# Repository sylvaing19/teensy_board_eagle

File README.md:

# teensy_board_eagle
Eagle library for integrating teensy boards.

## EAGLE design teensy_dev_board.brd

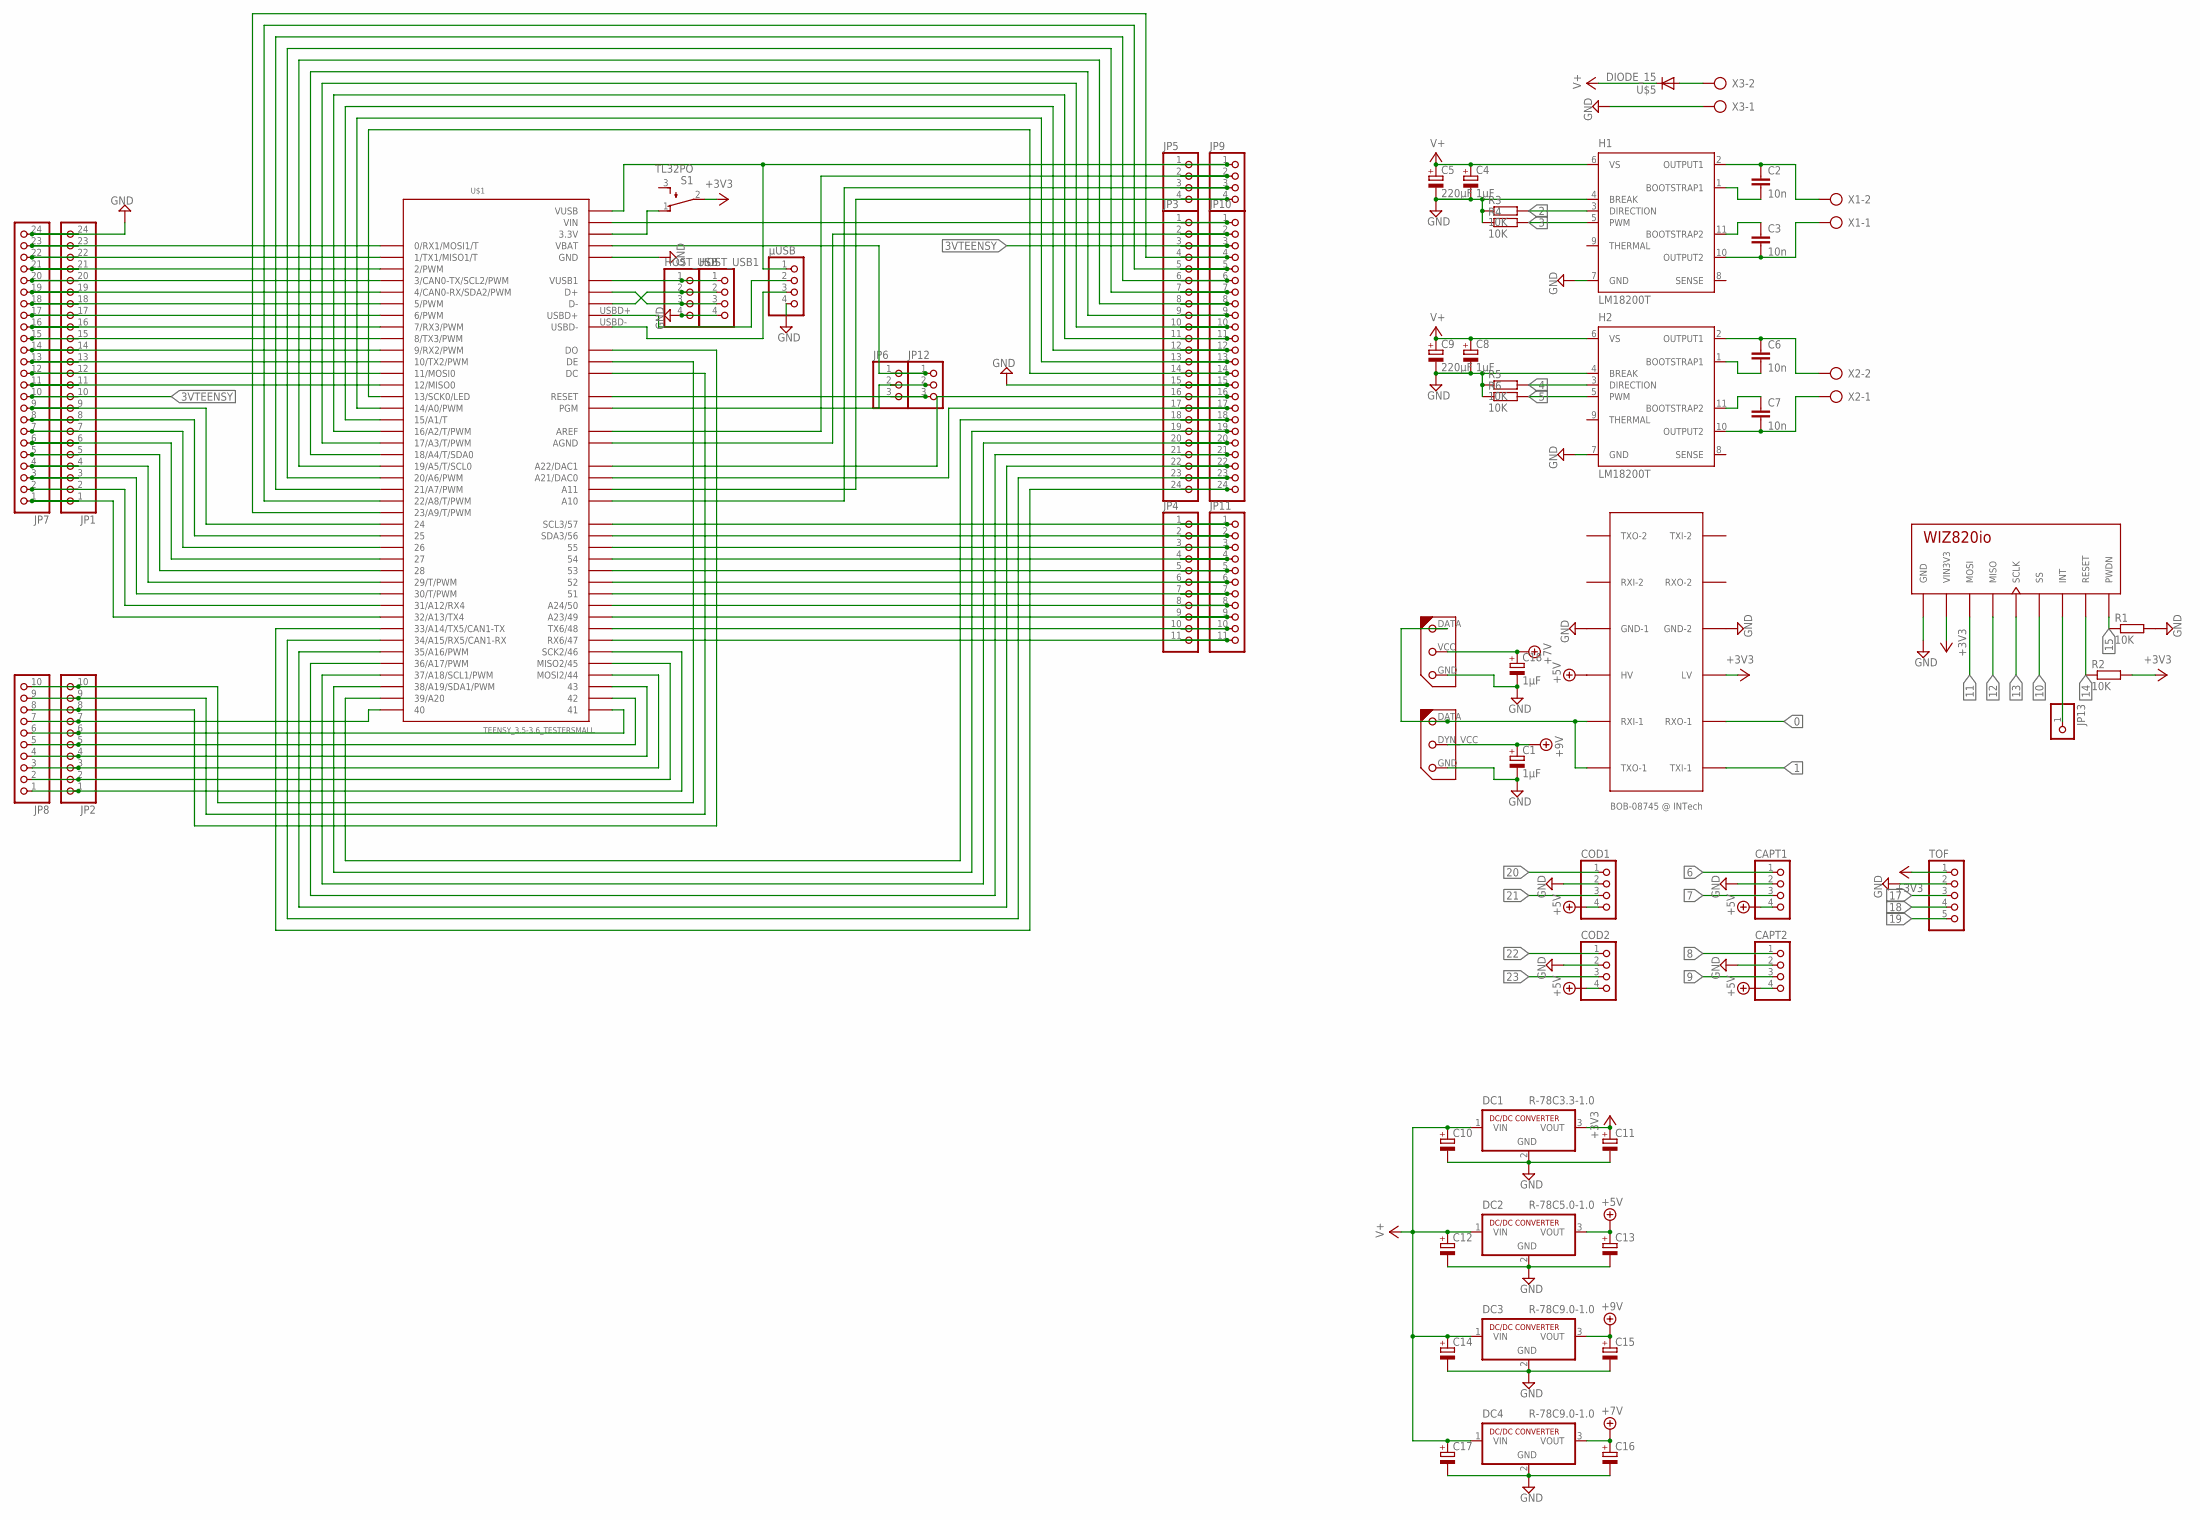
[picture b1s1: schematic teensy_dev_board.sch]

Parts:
C1, C18: 1µF; E2,5-6E
C2, C3, C6, C7: 10n; C050-025X075
C4, C8: 1µF; E2,5-7
C5, C9: 220µF; E2,5-7
C10, C11, C12, C13, C14, C15, C16, C17: CPOL-EUE2.5-6; E2,5-6
CAPT1, CAPT2: PINHD-1X4B; 1X04B
COD1, COD2: PINHD-1X4B; 1X04B
DC1: R-78C3.3-1.0; SIP3
DC2: R-78C5.0-1.0; SIP3
DC3, DC4: R-78C9.0-1.0; SIP3
H1, H2: LM18200T; TO-220-11
HOST_USB, HOST_USB1: PINHD-1X4; 1X04
JP1, JP3, JP7, JP10: PINHD-1X24; 1X24
JP2, JP8: PINHD-1X10; 1X10
JP4, JP11: PINHD-1X11; 1X11
JP5, JP9: PINHD-1X4; 1X04
JP6, JP12: PINHD-1X3; 1X03
JP13: PINHD-1X1; 1X01
R1, R2, R3, R4, R5, R6: 10K; 0204/7
S1: TL32PO; TL3XPO
TOF: PINHD-1X5B; 1X05B
U$1: TEENSY_3.5-3.6_TESTERSMALL; TEENSY_3.5-3.6_TESTER_SMALL
U$2: BOB-08745
U$3: DYNAMIXEL-1X03AX; DYNAMIXEL_AX_1X03
U$4: WIZ820IO; WIZ820
U$5: DIODE_15; DO201-15
U$6: DYNAMIXEL-1X03XL; DYNAMIXEL_XL_1X03
X1, X2, X3: AK300/2
µUSB: PINHD-1X4; 1X04

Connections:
0: JP1.23, JP7.23, U$1.0 (0/RX1/MOSI1/T), U$2.RXO-1
1: JP1.22, JP7.22, U$1.1 (1/TX1/MISO1/T), U$2.TXI-1
2: H1.3 (DIRECTION), JP1.21, JP7.21, R3.2, U$1.2 (2/PWM)
3: H1.5 (PWM), JP1.20, JP7.20, R4.2, U$1.3 (3/CAN0-TX/SCL2/PWM)
3VTEENSY: JP1.10, JP3.3, JP7.10, JP10.3, S1.1 (O), U$1.3.3V, U$1.3.3V2 (3.3V), U$1.3.3V3 (3.3V), U$1.3.3V4 (3.3V)
4: H2.3 (DIRECTION), JP1.19, JP7.19, R5.2, U$1.4 (4/CAN0-RX/SDA2/PWM)
5: H2.5 (PWM), JP1.18, JP7.18, R6.2, U$1.5 (5/PWM)
6: CAPT1.1, JP1.17, JP7.17, U$1.6 (6/PWM)
7: CAPT1.3, JP1.16, JP7.16, U$1.7 (7/RX3/PWM)
8: CAPT2.1, JP1.15, JP7.15, U$1.8 (8/TX3/PWM)
9: CAPT2.3, JP1.14, JP7.14, U$1.9 (9/RX2/PWM)
10: JP1.13, JP7.13, U$1.10 (10/TX2/PWM), U$4.SS
11: JP1.12, JP7.12, U$1.11 (11/MOSI0), U$4.MOSI
12: JP1.11, JP7.11, U$1.12 (12/MISO0), U$4.MISO
13: JP3.14, JP10.14, U$1.13 (13/SCK0/LED), U$4.SCLK
14: JP3.13, JP10.13, R2.1, U$1.14/A0 (14/A0/PWM), U$4.RESET
15: JP3.12, JP10.12, R1.1, U$1.15/A1 (15/A1/T), U$4.PWDN
16: JP3.11, JP10.11, U$1.16/A2 (16/A2/T/PWM)
17: JP3.10, JP10.10, TOF.3, U$1.17/A3 (17/A3/T/PWM)
18: JP3.9, JP10.9, TOF.4, U$1.18/A4 (18/A4/T/SDA0)
19: JP3.8, JP10.8, TOF.5, U$1.19/A5 (19/A5/T/SCL0)
20: COD1.1, JP3.7, JP10.7, U$1.20/A6 (20/A6/PWM)
21: COD1.3, JP3.6, JP10.6, U$1.21/A7 (21/A7/PWM)
22: COD2.1, JP3.5, JP10.5, U$1.22/A8 (22/A8/T/PWM)
23: COD2.3, JP3.4, JP10.4, U$1.23/A9 (23/A9/T/PWM)
24: JP1.9, JP7.9, U$1.24
25: JP1.8, JP7.8, U$1.25
26: JP1.7, JP7.7, U$1.26
27: JP1.6, JP7.6, U$1.27
28: JP1.5, JP7.5, U$1.28
29: JP1.4, JP7.4, U$1.29 (29/T/PWM)
30: JP1.3, JP7.3, U$1.30 (30/T/PWM)
31: JP1.2, JP7.2, U$1.31/A12 (31/A12/RX4)
32: JP1.1, JP7.1, U$1.32/A13 (32/A13/TX4)
33: JP3.24, JP10.24, U$1.33/A14 (33/A14/TX5/CAN1-TX)
34: JP3.23, JP10.23, U$1.34/A15 (34/A15/RX5/CAN1-RX)
35: JP3.22, JP10.22, U$1.35/A16 (35/A16/PWM)
36: JP3.21, JP10.21, U$1.36/A17 (36/A17/PWM)
37: JP3.20, JP10.20, U$1.37/A18 (37/A18/SCL1/PWM)
38: JP3.19, JP10.19, U$1.38/A19 (38/A19/SDA1/PWM)
39: JP3.18, JP10.18, U$1.39/A20
40: JP2.7, JP8.7, U$1.40
41: JP2.6, JP8.6, U$1.41
42: JP2.5, JP8.5, U$1.42
43: JP2.4, JP8.4, U$1.43
44: JP2.3, JP8.3, U$1.44 (MOSI2/44)
45: JP2.2, JP8.2, U$1.45 (MISO2/45)
46: JP2.1, JP8.1, U$1.46 (SCK2/46)
47: JP4.11, JP11.11, U$1.47 (RX6/47)
48: JP4.10, JP11.10, U$1.48 (TX6/48)
49: JP4.9, JP11.9, U$1.49 (A23/49)
50: JP4.8, JP11.8, U$1.50 (A24/50)
51: JP4.7, JP11.7, U$1.51
52: JP4.6, JP11.6, U$1.52
53: JP4.5, JP11.5, U$1.53
54: JP4.4, JP11.4, U$1.54
55: JP4.3, JP11.3, U$1.55
56: JP4.2, JP11.2, U$1.56 (SDA3/56)
57: JP4.1, JP11.1, U$1.57 (SCL3/57)
+3V3: C11.+, DC1.3 (VOUT), R2.2, S1.2, TOF.1, U$2.LV, U$4.VIN1 (VIN3V3), U$4.VIN2 (VIN3V3)
+5V: C13.+, CAPT1.4, CAPT2.4, COD1.4, COD2.4, DC2.3 (VOUT), U$2.HV
+7V: C16.+, C18.+, DC4.3 (VOUT), U$6.VCC (DYN_VCC)
+9V: C1.+, C15.+, DC3.3 (VOUT), U$3.DYN_VCC
A10: JP5.3, JP9.3, U$1.A10
A11: JP5.4, JP9.4, U$1.A11
AGND: JP3.2, JP10.2, U$1.AGND
AREF: JP5.2, JP9.2, U$1.AREF
D+: HOST_USB.2, HOST_USB1.2, U$1.D-
D-: HOST_USB.3, HOST_USB1.3, U$1.D+
DAC0: JP3.17, JP10.17, U$1.A21 (A21/DAC0)
DAC1: JP3.16, JP10.16, U$1.A22 (A22/DAC1)
DC: JP2.9, JP8.9, U$1.DC
DE: JP2.10, JP8.10, U$1.DE
DO: JP2.8, JP8.8, U$1.DO
GND: C1.-, C4.-, C5.-, C8.-, C9.-, C10.-, C11.-, C12.-, C13.-, C14.-, C15.-, C16.-, C17.-, C18.-, CAPT1.2, CAPT2.2, COD1.2, COD2.2, DC1.2 (GND), DC2.2 (GND), DC3.2 (GND), DC4.2 (GND), H1.4 (BREAK), H1.7 (GND), H2.4 (BREAK), H2.7 (GND), HOST_USB.4, HOST_USB1.4, JP1.24, JP3.15, JP7.24, JP10.15, R1.2, R3.1, R4.1, R5.1, R6.1, TOF.2, U$1.GND, U$1.GND1 (GND), U$1.GND2 (GND), U$1.GND3 (GND), U$1.GND4 (GND), U$1.GND5 (GND), U$1.GND6 (GND), U$2.GND-1, U$2.GND-2, U$3.GND, U$4.GND1 (GND), U$4.GND2 (GND), U$4.GND3 (GND), U$6.GND, X3.1, µUSB.4
unnamed: U$2.RXI-1, U$2.TXO-1, U$3.DATA, U$6.DATA
unnamed: C2.1, H1.2 (OUTPUT1), X1.2
unnamed: C2.2, H1.1 (BOOTSTRAP1)
unnamed: C3.2, H1.10 (OUTPUT2), X1.1
unnamed: C3.1, H1.11 (BOOTSTRAP2)
unnamed: JP13.1, U$4.INT
unnamed: U$5.A (A+), X3.2
unnamed: C6.1, H2.2 (OUTPUT1), X2.2
unnamed: C6.2, H2.1 (BOOTSTRAP1)
unnamed: C7.2, H2.10 (OUTPUT2), X2.1
unnamed: C7.1, H2.11 (BOOTSTRAP2)
PGM: JP6.2, JP12.2, U$1.PGM
RESET: JP6.3, JP12.3, U$1.RESET
USBD+: U$1.USBD+, µUSB.2
USBD-: U$1.USBD-, µUSB.3
V+: C4.+, C5.+, C8.+, C9.+, C10.+, C12.+, C14.+, C17.+, DC1.1 (VIN), DC2.1 (VIN), DC3.1 (VIN), DC4.1 (VIN), H1.6 (VS), H2.6 (VS), U$5.C (C-)
VBAT: JP6.1, JP12.1, U$1.VBAT
VIN: JP3.1, JP10.1, U$1.VIN
VUSB: JP5.1, JP9.1, U$1.VUSB, µUSB.1
VUSB1: HOST_USB.1, HOST_USB1.1, U$1.VUSB1

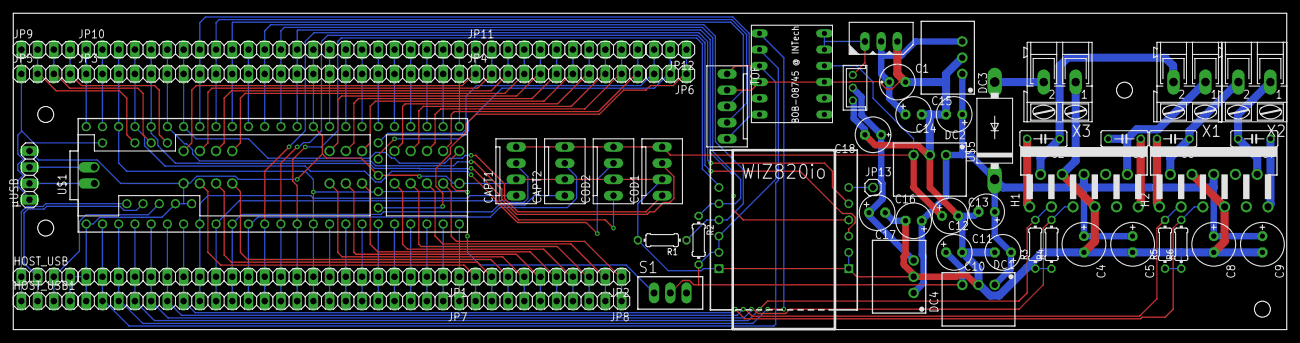
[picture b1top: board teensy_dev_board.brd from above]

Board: 2 copper layers, 199.4 x 49.5 mm, 61 parts (0 on the bottom side), 95 nets.

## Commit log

2017-05-30 first version of eagle lib + 3D printable support for teensy 3.5-3.6
2017-06-01 update dimensions
2017-06-01 update skp
2017-06-02 maj brd
2017-06-21 add schematics board and gerber files
